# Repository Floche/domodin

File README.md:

# domodin
Extension fil pilote sur rail DIN pour Raspberry Pi

https://domodin.wordpress.com/

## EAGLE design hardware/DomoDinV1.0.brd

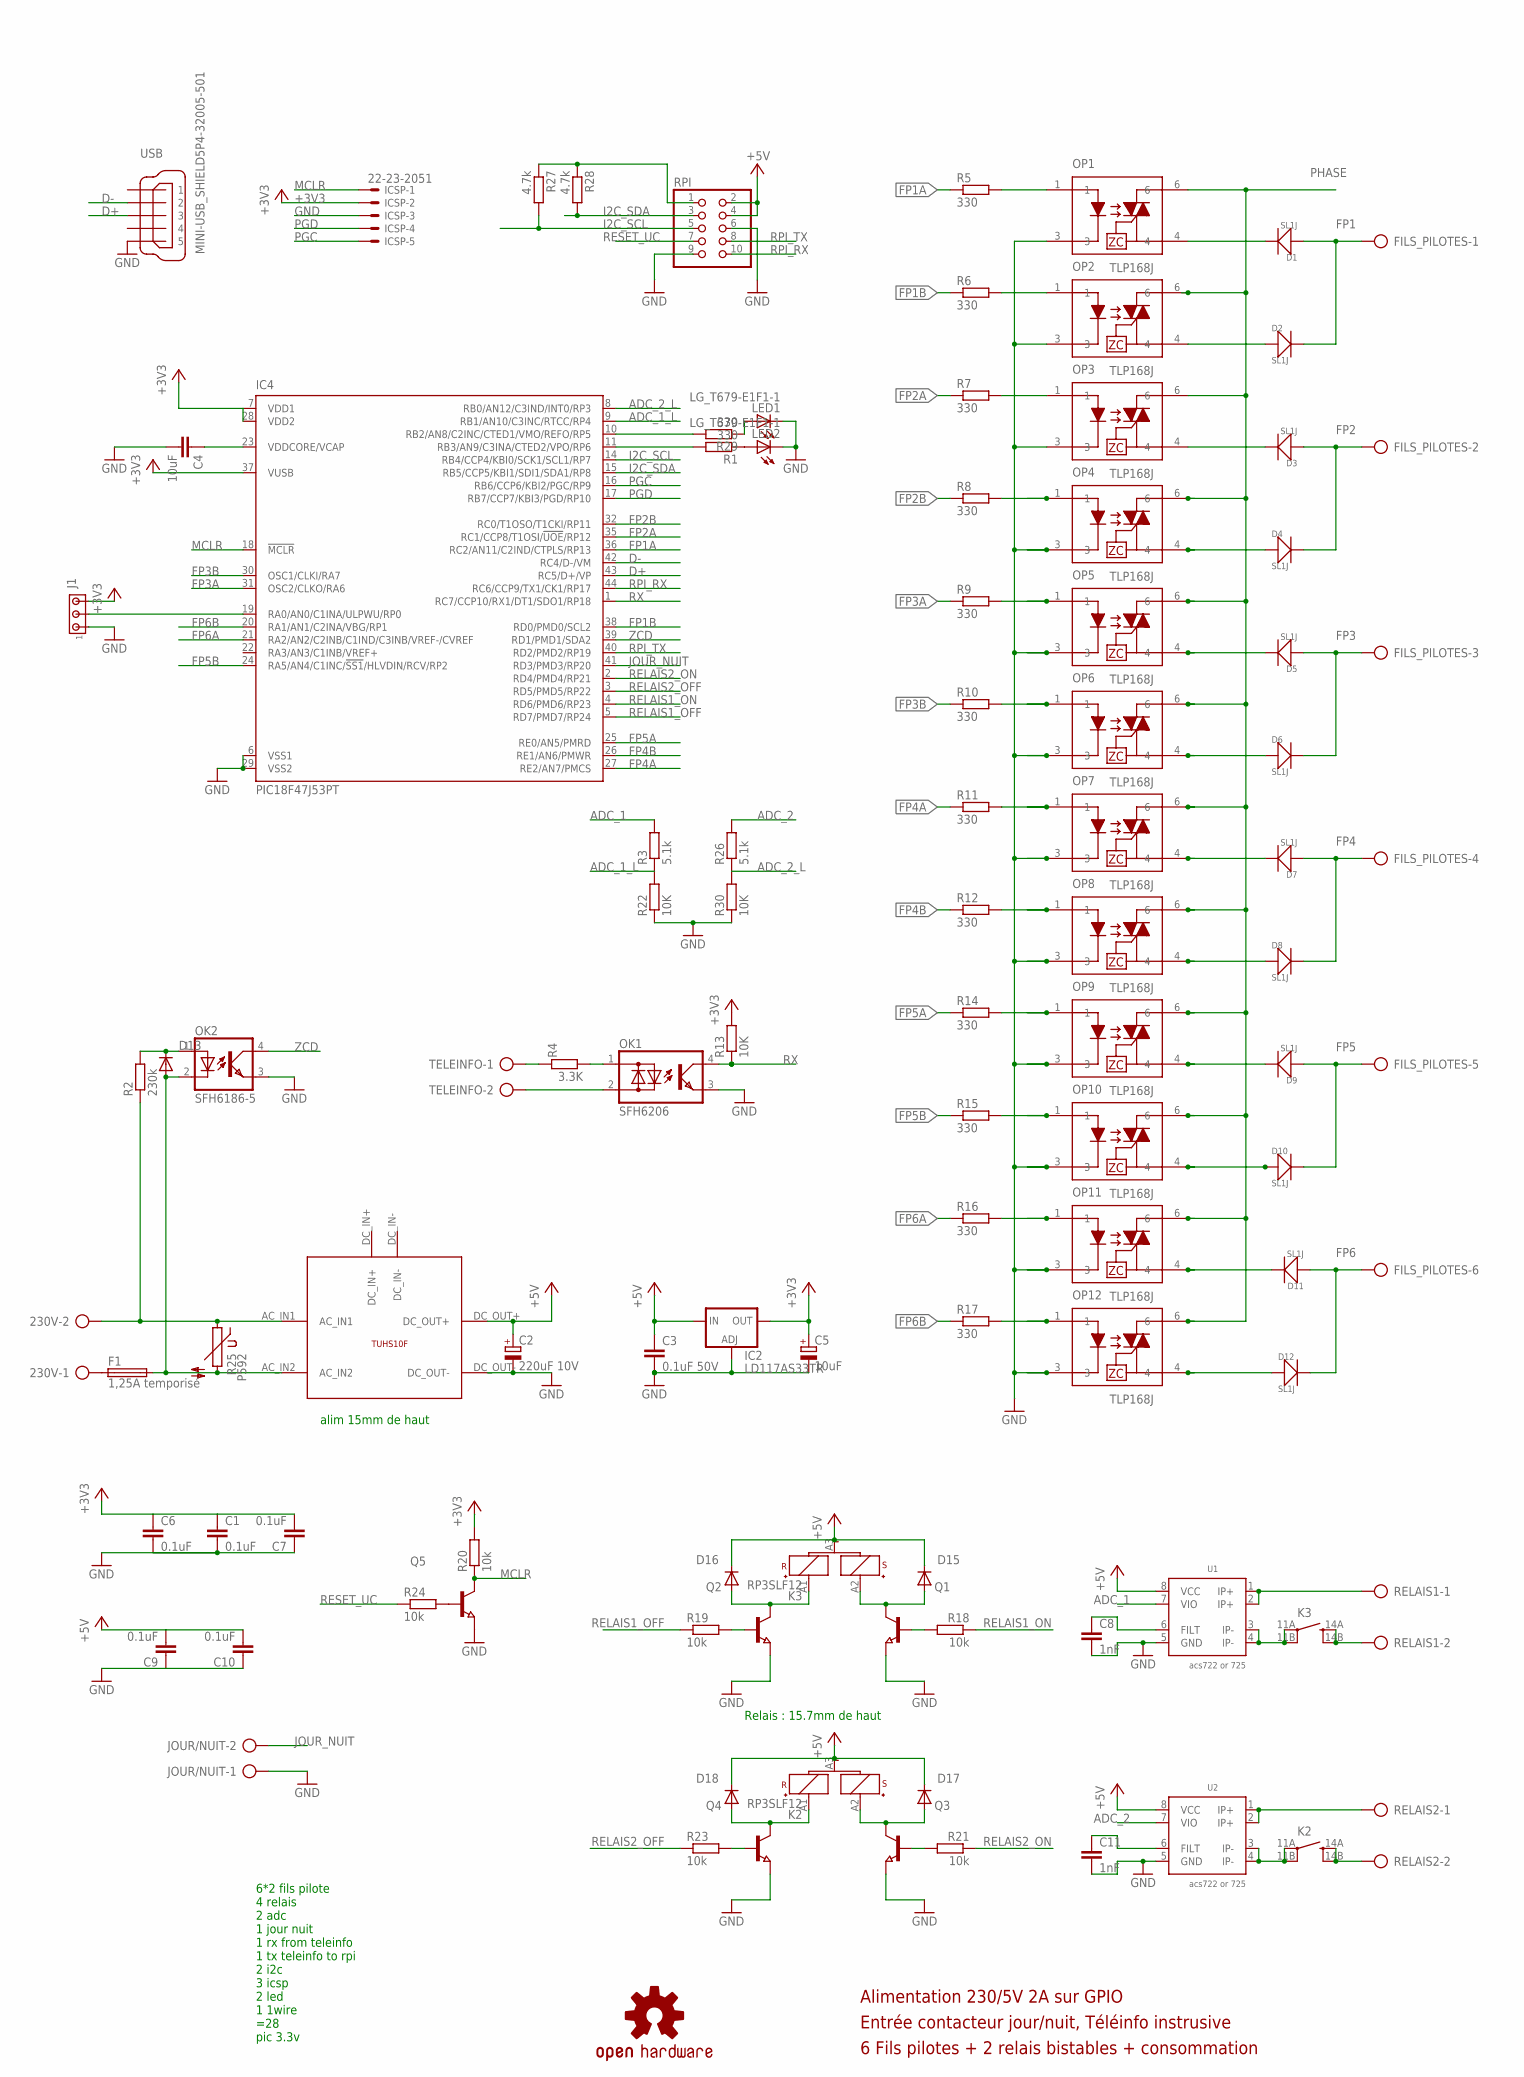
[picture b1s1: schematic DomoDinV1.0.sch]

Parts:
230V: AK500/2
C1, C6, C7, C9, C10: 0.1uF; C0603
C2: 220uF 10V; E5-8,5
C3: 0.1uF 50V; C1206
C4: 10uF; C1210K
C5: 10uF; C/6032-28R
C8, C11: 1nF; C0402
D1, D2, D3, D4, D5, D6, D7, D8, D9, D10, D11, D12: SL1J; DO-214AC
D13, D15, D16, D17, D18: CGRM4001-G; SOD-123_MINI-SMA
F1: 1,25A temporisé; TE5
FILS_PILOTES: AK500/6
IC2: LD117AS33TR; SOT223
IC4: PIC18F47J53PT; TQFP44
ICSP: 22-23-2051
J1: MTA03-100; 10X03MTA
JOUR/NUIT: AK500/2
K2, K3: RP3SLF12; RP-SLF
LED1, LED2: LG_T679-E1F1-1; PLCC2
LOGO1: OSHW-LOGOL; OSHW-LOGO-L
OK1: SFH6206; DIL4-SMD
OK2: SFH6186-5; SMD4-7
OP1, OP2, OP3, OP4, OP5, OP6, OP7, OP8, OP9, OP10, OP11, OP12: TLP168J; MFSOP-4-HANDSOLDER
Q1, Q2, Q3, Q4, Q5: NPN-TRANSISTOR_SOT23; SOT23
R1, R5, R6, R7, R8, R9, R10, R11, R12, R14, R15, R16, R17, R29: 330; R0805
R2: 230k; 0204/7
R3, R26: 5.1k; R0402
R4: 3.3K; R0805
R13: 10K; R0805
R18, R19, R20, R21, R23, R24: 10k; R0805
R22, R30: 10K; R0402
R25: P592
R27, R28: 4.7k; R0805
RELAIS1, RELAIS2: AK500/2
RPI: PINHD-2X5; 2X05
TELEINFO: AK500/2
U1, U2: acs722 or 725; SO08
U$1: TUHS10F; TUHS10F05
USB: MINI-USB_SHIELD5P4-32005-501; 32005-501

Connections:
+3V3: C1.1, C5.+, C6.1, C7.2, IC2.4 (OUT), IC4.7 (VDD1), IC4.28 (VDD2), IC4.37 (VUSB), ICSP.2, J1.3, R13.2, R20.2
+5V: C2.+, C3.1, C9.2, C10.2, D15.C, D16.C, D17.C, D18.C, IC2.3 (IN), K2.A3 (-), K3.A3 (-), RPI.2, RPI.4, U1.8 (VCC), U2.8 (VCC), U$1.DC_OUT+
ADC_1: R3.2, U1.7 (VIO)
ADC_1_L: IC4.9 (RB1/AN10/C3INC/RTCC/RP4), R3.1, R22.2
ADC_2: R26.2, U2.7 (VIO)
ADC_2_L: IC4.8 (RB0/AN12/C3IND/INT0/RP3), R26.1, R30.2
D+: IC4.43 (RC5/D+/VP), USB.3
D-: IC4.42 (RC4/D-/VM), USB.2
FP1: D1.1 (+), D2.2 (-), FILS_PILOTES.1
FP1A: IC4.36 (RC2/AN11/C2IND/CTPLS/RP13), R5.1
FP1B: IC4.38 (RD0/PMD0/SCL2), R6.1
FP2: D3.1 (+), D4.2 (-), FILS_PILOTES.2
FP2A: IC4.35 (RC1/CCP8/T1OSI/!UOE!/RP12), R7.1
FP2B: IC4.32 (RC0/T1OSO/T1CKI/RP11), R8.1
FP3: D5.1 (+), D6.2 (-), FILS_PILOTES.3
FP3A: IC4.31 (OSC2/CLKO/RA6), R9.1
FP3B: IC4.30 (OSC1/CLKI/RA7), R10.1
FP4: D7.1 (+), D8.2 (-), FILS_PILOTES.4
FP4A: IC4.27 (RE2/AN7/PMCS), R11.1
FP4B: IC4.26 (RE1/AN6/PMWR), R12.1
FP5: D9.1 (+), D10.2 (-), FILS_PILOTES.5
FP5A: IC4.25 (RE0/AN5/PMRD), R14.1
FP5B: IC4.24 (RA5/AN4/C1INC/!SS1!/HLVDIN/RCV/RP2), R15.1
FP6: D11.1 (+), D12.2 (-), FILS_PILOTES.6
FP6A: IC4.21 (RA2/AN2/C2INB/C1IND/C3INB/VREF-/CVREF), R16.1
FP6B: IC4.20 (RA1/AN1/C2INA/VBG/RP1), R17.1
GND: C1.2, C2.-, C3.2, C4.2, C5.-, C6.2, C7.1, C8.2, C9.1, C10.1, C11.2, IC2.1 (ADJ), IC4.6 (VSS1), IC4.29 (VSS2), ICSP.3, J1.1, JOUR/NUIT.1, LED1.C, LED2.C, OK1.3 (E), OK2.3 (EMIT), OP1.3, OP2.3, OP3.3, OP4.3, OP5.3, OP6.3, OP7.3, OP8.3, OP9.3, OP10.3, OP11.3, OP12.3, Q1.2 (E), Q2.2 (E), Q3.2 (E), Q4.2 (E), Q5.2 (E), R22.1, R30.1, RPI.6, RPI.9, U1.5 (GND), U2.5 (GND), U$1.DC_OUT-, USB.5
I2C_SCL: IC4.14 (RB4/CCP4/KBI0/SCK1/SCL1/RP7), R27.2, RPI.5
I2C_SDA: IC4.15 (RB5/CCP5/KBI1/SDI1/SDA1/RP8), R28.2, RPI.3
JOUR_NUIT: IC4.41 (RD3/PMD3/RP20), JOUR/NUIT.2
MCLR: IC4.18 (!MCLR), ICSP.1, Q5.3 (C), R20.1
unnamed: R4.1, TELEINFO.1
unnamed: OK1.2 (AC2), TELEINFO.2
unnamed: RELAIS1.1, U1.1 (IP+), U1.2 (IP+)
unnamed: IC4.10 (RB2/AN8/C2INC/CTED1/VMO/REFO/RP5), R29.2
unnamed: OK1.1 (AC1), R4.2
unnamed: K2.11A (PA), K2.11B (PB), U2.3 (IP-), U2.4 (IP-)
unnamed: OP1.1, R5.2
unnamed: OP2.1, R6.2
unnamed: D1.2 (-), OP1.4
unnamed: OP3.1, R7.2
unnamed: OP5.1, R9.2
unnamed: OP6.1, R10.2
unnamed: OP7.1, R11.2
unnamed: OP8.1, R12.2
unnamed: OP4.1, R8.2
unnamed: D2.1 (+), OP2.4
unnamed: 230V.1, F1.1
unnamed: K3.11A (PA), K3.11B (PB), U1.3 (IP-), U1.4 (IP-)
unnamed: OP9.1, R14.2
unnamed: K3.14A (SA), K3.14B (SB), RELAIS1.2
unnamed: Q1.1 (B), R18.2
unnamed: D3.2 (-), OP3.4
unnamed: LED2.A, R1.1
unnamed: D5.2 (-), OP5.4
unnamed: D4.1 (+), OP4.4
unnamed: D7.2 (-), OP7.4
unnamed: K2.14A (SA), K2.14B (SB), RELAIS2.2
unnamed: D15.A, K3.A2 (S+), Q1.3 (C)
unnamed: D6.1 (+), OP6.4
unnamed: Q2.1 (B), R19.2
unnamed: D8.1 (+), OP8.4
unnamed: OP10.1, R15.2
unnamed: D16.A, K3.A1 (R+), Q2.3 (C)
unnamed: Q3.1 (B), R21.2
unnamed: D17.A, K2.A2 (S+), Q3.3 (C)
unnamed: Q4.1 (B), R23.2
unnamed: D18.A, K2.A1 (R+), Q4.3 (C)
unnamed: 230V.2, R2.1, R25.1, U$1.AC_IN1
unnamed: C4.1, IC4.23 (VDDCORE/VCAP)
unnamed: RELAIS2.1, U2.1 (IP+), U2.2 (IP+)
unnamed: Q5.1 (B), R24.2
unnamed: D9.2 (-), OP9.4
unnamed: IC4.11 (RB3/AN9/C3INA/CTED2/VPO/RP6), R1.2
unnamed: LED1.A, R29.1
unnamed: IC4.19 (RA0/AN0/C1INA/ULPWU/RP0), J1.2
unnamed: OP11.1, R16.2
unnamed: OP12.1, R17.2
unnamed: D10.1 (+), OP10.4
unnamed: R27.1, R28.1, RPI.1
unnamed: D12.1 (+), OP12.4
unnamed: C11.1, U2.6 (FILT)
unnamed: D13.C, OK2.1 (A), R2.2
unnamed: C8.1, U1.6 (FILT)
PGC: IC4.16 (RB6/CCP6/KBI2/PGC/RP9), ICSP.5
PGD: IC4.17 (RB7/CCP7/KBI3/PGD/RP10), ICSP.4
PHASE: D13.A, F1.2, OK2.2 (C), OP1.6, OP2.6, OP3.6, OP4.6, OP5.6, OP6.6, OP7.6, OP8.6, OP9.6, OP10.6, OP11.6, OP12.6, R25.2, U$1.AC_IN2
RELAIS1_OFF: IC4.5 (RD7/PMD7/RP24), R19.1
RELAIS1_ON: IC4.4 (RD6/PMD6/RP23), R18.1
RELAIS2_OFF: IC4.3 (RD5/PMD5/RP22), R23.1
RELAIS2_ON: IC4.2 (RD4/PMD4/RP21), R21.1
RESET_UC: R24.1, RPI.7
RPI_RX: IC4.44 (RC6/CCP9/TX1/CK1/RP17), RPI.10
RPI_TX: IC4.40 (RD2/PMD2/RP19), RPI.8
RX: IC4.1 (RC7/CCP10/RX1/DT1/SDO1/RP18), OK1.4 (C), R13.1
S$1: D11.2 (-), OP11.4
ZCD: IC4.39 (RD1/PMD1/SDA2), OK2.4 (COL)

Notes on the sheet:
6 Fils pilotes + 2 relais bistables + consommation
Entrée contacteur jour/nuit, Téléinfo instrusive
Alimentation 230/5V 2A sur GPIO
6*2 fils pilote 4 relais 2 adc 1 jour nuit 1 rx from teleinfo 1 tx teleinfo to rpi 2 i2c 3 icsp 2 led 1 1wire =28 pic 3.3v
alim 15mm de haut
Relais : 15.7mm de haut

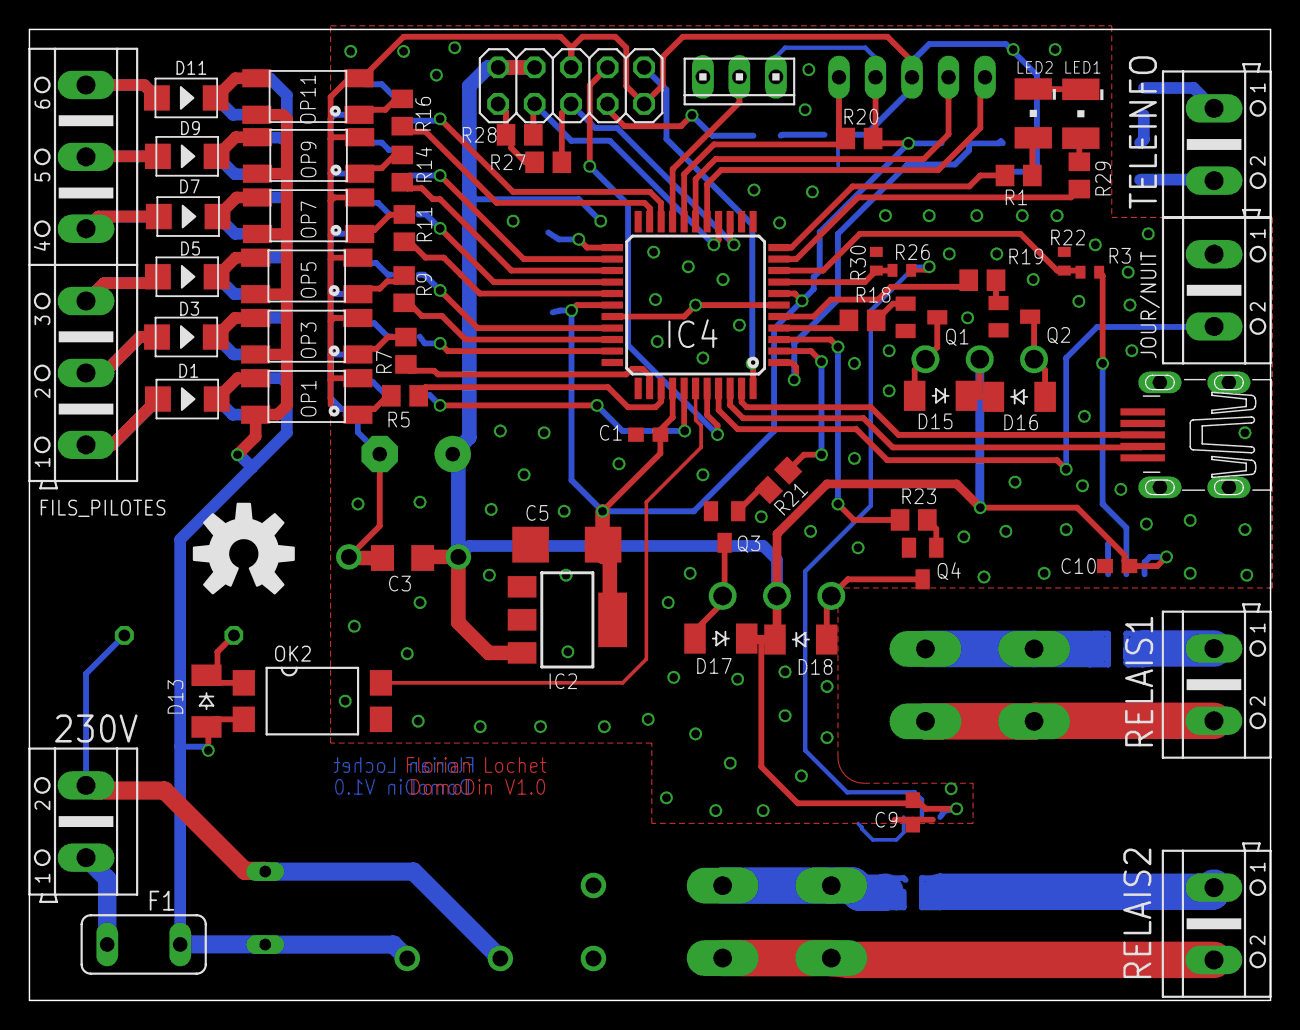
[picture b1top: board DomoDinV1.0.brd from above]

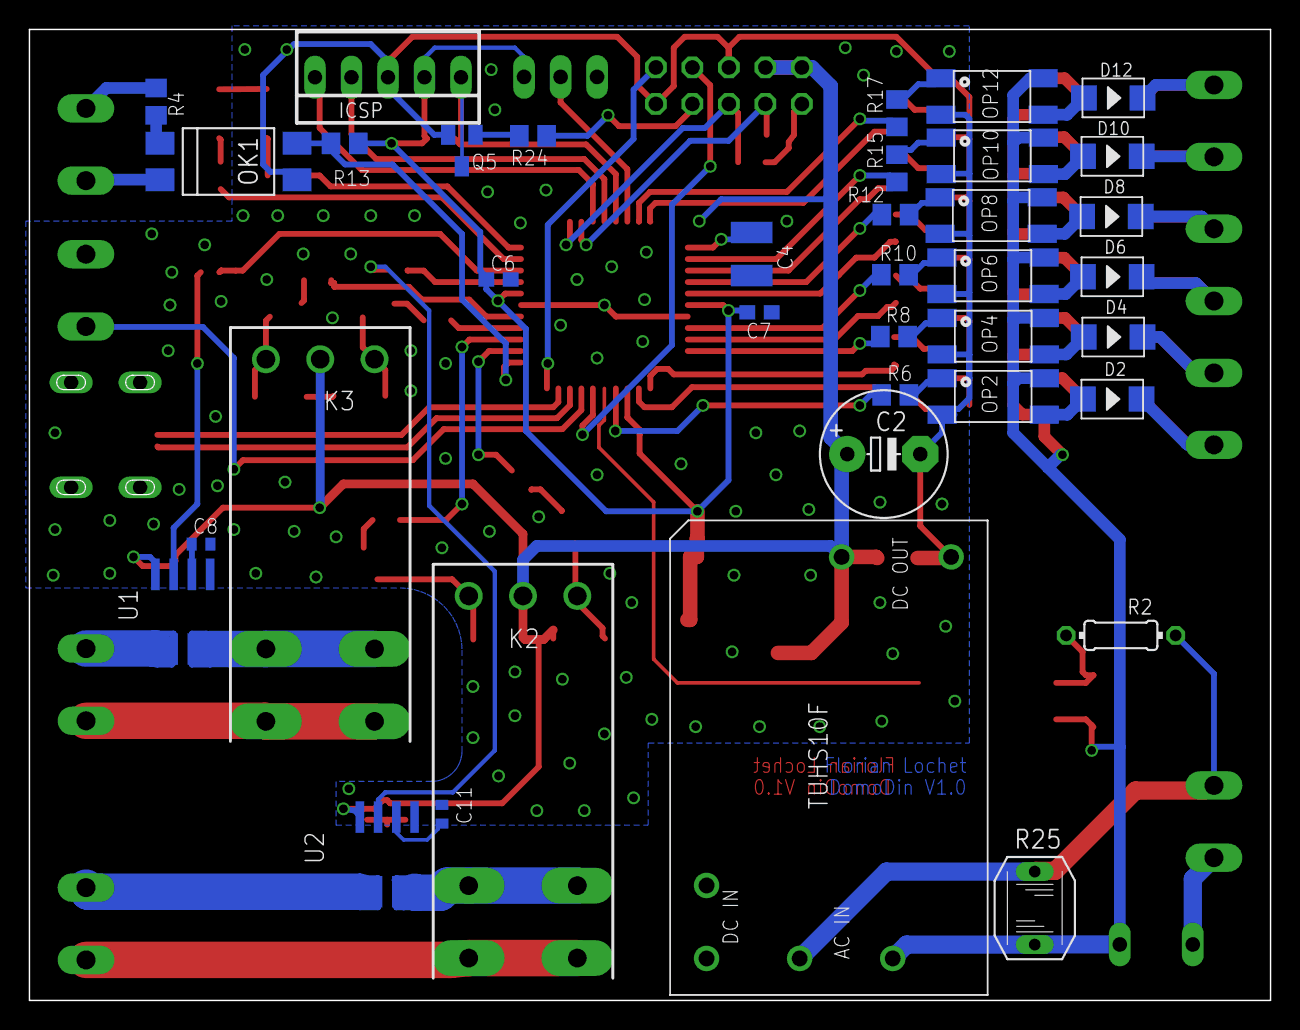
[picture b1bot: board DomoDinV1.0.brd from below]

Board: 2 copper layers, 86.4 x 67.6 mm, 98 parts (37 on the bottom side), 97 nets.

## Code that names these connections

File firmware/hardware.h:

#ifndef HARDWARE_H
#define	HARDWARE_H

#define LED1 	PIN_B2
#define LED2 	PIN_B3

#define FP1A    PIN_C2
#define FP1B    PIN_D0
#define FP2A    PIN_C1
#define FP2B    PIN_C0
#define FP3A    PIN_A6
#define FP3B    PIN_A7
#define FP4A    PIN_E2
#define FP4B    PIN_E1
#define FP5A    PIN_E0
#define FP5B    PIN_A5
#define FP6A    PIN_A2
#define FP6B    PIN_A1

#define RELAIS1_ON  PIN_D6
#define RELAIS1_OFF PIN_D7
#define RELAIS1_ADC	10

#define RELAIS2_ON  PIN_D4
#define RELAIS2_OFF PIN_D5
#define RELAIS2_ADC	12

#define DELAIS_RELAIS_MS 30

#define ONE_WIRE        PIN_A0
#define ZCD             PIN_D1
#define CONTACT_IO      PIN_D3
#define SERIAL_FROM_RPI PIN_D2

#define ADC_RELAIS_1    
#define ADC_RELAIS_2    

#endif	/* HARDWARE_H */

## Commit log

2015-09-30 Adding schematic and bootloader
2015-09-30 Move bootloader to firmware/bootloader
2015-09-30 cleaning and calculating checksum when bootloading
2015-10-02 adding script for domoticz, and bootloader compiled
2015-10-07 Cleaning code
2015-10-07 adding script
2015-10-13 Removal of current order
2015-10-13 Adding ADC measure
2015-11-18 Current measure working
    Correcting ADC reading.
    Adding average and maximum detection

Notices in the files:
parts and their libraries:
SparkFun-Aesthetics: Licensing: Creative Commons ShareAlike 4.0 International - https://creativecommons.org/licenses/by-sa/4.0
